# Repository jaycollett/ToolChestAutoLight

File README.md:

# ToolChestAutoLight
Simple MOSFET LED circuit for a tool chest

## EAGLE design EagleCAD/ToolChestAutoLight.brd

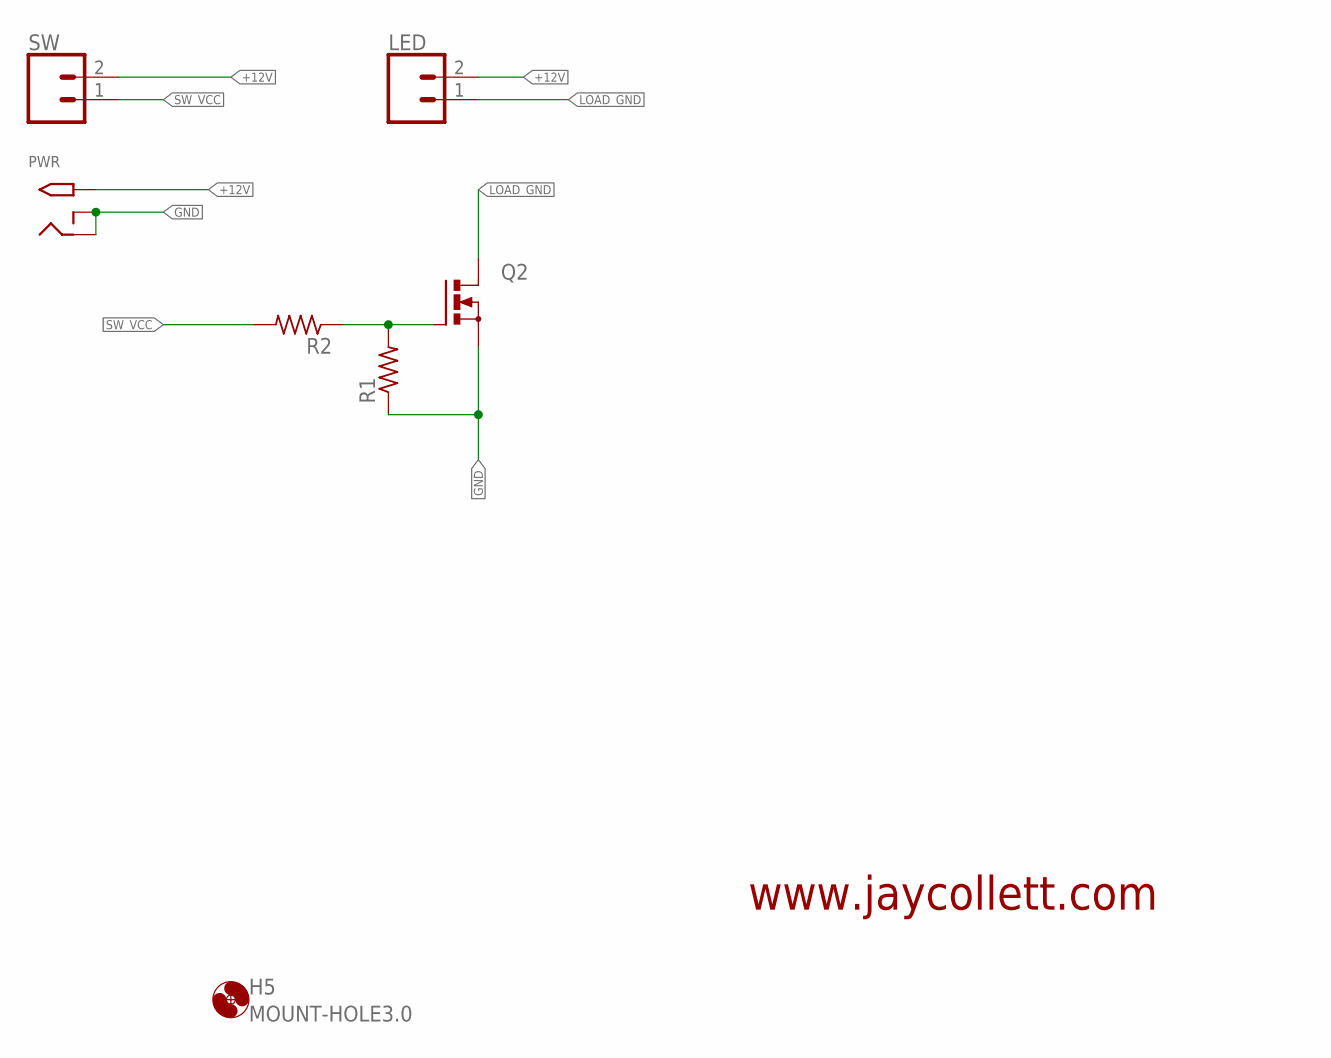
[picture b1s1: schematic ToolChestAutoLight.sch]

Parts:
H5: MOUNT-HOLE3.0; 3,0
LED: CONN_02LOCK_LONGPADS; 1X02_LOCK_LONGPADS
PWR: 2.1MMJACKTHM; PJ-102A
Q2: PMOSFET_NTO220BH; TO220BH
R1, R2: R-US_0204/5; 0204/5
SW: CONN_02LOCK_LONGPADS; 1X02_LOCK_LONGPADS

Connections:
+12V: LED.2, PWR.TIP, SW.2
GND: PWR.RING, PWR.RING_SW, Q2.S, R1.1
LOAD_GND: LED.1, Q2.D
unnamed: Q2.G, R1.2, R2.1
SW_VCC: R2.2, SW.1

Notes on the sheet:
www.jaycollett.com

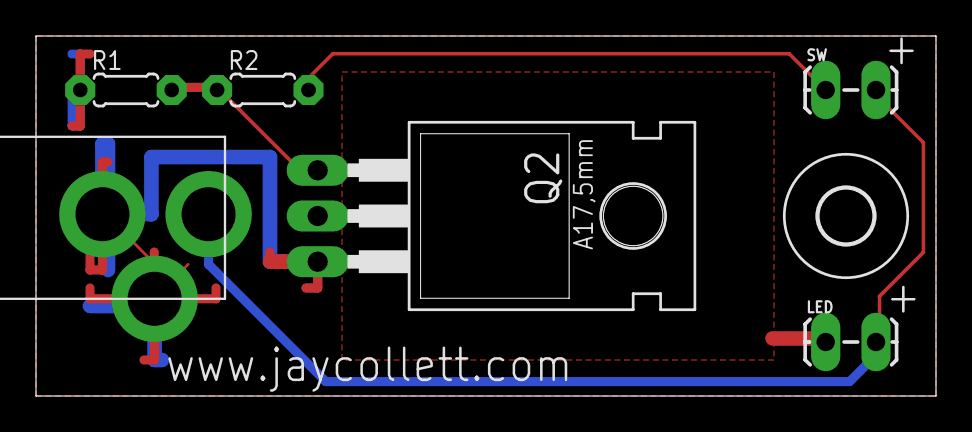
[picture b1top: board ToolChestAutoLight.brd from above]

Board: 2 copper layers, 50.0 x 20.0 mm, 7 parts (0 on the bottom side), 5 nets.

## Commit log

2019-12-28 First version of PCB
2020-01-12 add images for project

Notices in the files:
parts and their libraries:
SparkFun-Connectors: Licensing: Creative Commons ShareAlike 4.0 International - https://creativecommons.org/licenses/by-sa/4.0
